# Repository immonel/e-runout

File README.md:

# e-runout

This project is used to measure electrical runout by comparing measurements from touching probe sensors and Eddy current probes simultaneously.

Technologies and frameworks used in the project include Docker, React, Redux, Bootstrap, Node.js, Express, MongoDB and Socket.IO.

### Project structure
[client/](client/)  
Frontend React app code

[documentation/](documentation/)  
Documentation files

[hardware/](hardware/)  
PCB schematics

[mongodb/](mongodb/)  
MongoDB init scripts

[server/](server/)  
Backend Node.js app code

[teensy/](teensy/)  
Teensy microcontroller C++ code

----
## Getting started

### Production

1. Fill out environment variables and rename the .env file:
```sh
$ mv .example.env .env
```

2. Start up the docker-compose stack:
```sh
$ docker-compose up
```

**NOTE:** Please keep in mind that buiding the `erunout` Docker image on Raspberry Pi will take a LONG time (~1h).

The application creates a Wi-Fi access point with environment variables `SSID` and `PASSPHRASE` given in the `.env` file.

IP address for the application is `10.0.10.1` by default and can be accessed after connecting to the WLAN network.

```
TODO: WAN access is currently not working on the wireless access point
```

### Development

1. Rename the .env file:
```sh
$ mv .env.example .env
```

2. Start up the development database:
```sh
$ docker-compose -f docker-compose.dev.yml up
```

3. Start up the development backend server (in the `server` folder):
```sh
server $ npm install
server $ npm run dev
```

4. Start up the development frontend server (in `client` folder):
```sh
client $ npm install
client $ npm start
```

5. Navigate to the development app at `localhost:3001`. The backend server is accessible from `localhost:3000` and the database admin interface from `localhost:8081`.

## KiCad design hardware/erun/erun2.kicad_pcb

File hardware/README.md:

# PCB schematics

This folder contains the KiCad (6.0) schematics for the project. The most recent schematics are named `erun2`. The project file is `erun2.kicad_pro` which is the easiest way to open all the schematics. The wiring diagram is in `erun2.kicad_sch` and PCB in `erun2.kicad_pcb`.

### Data sheets of components used
- [TXB0108PWR](https://www.ti.com/lit/ds/symlink/txb0108.pdf) Voltage level translator (5V->3.3V)
- [MC3486N](https://www.ti.com/lit/ds/symlink/mc3486.pdf) Differential line receiver
- [MCP3301](https://ww1.microchip.com/downloads/aemDocuments/documents/APID/ProductDocuments/DataSheets/21700E.pdf) 13-bit analog-to-digital converter
- [TPS79147DVBT](https://www.ti.com/lit/ds/symlink/tps79147-ep.pdf) Low-dropout regulator (WARNING: These break really easily due to ESD, be careful with these)

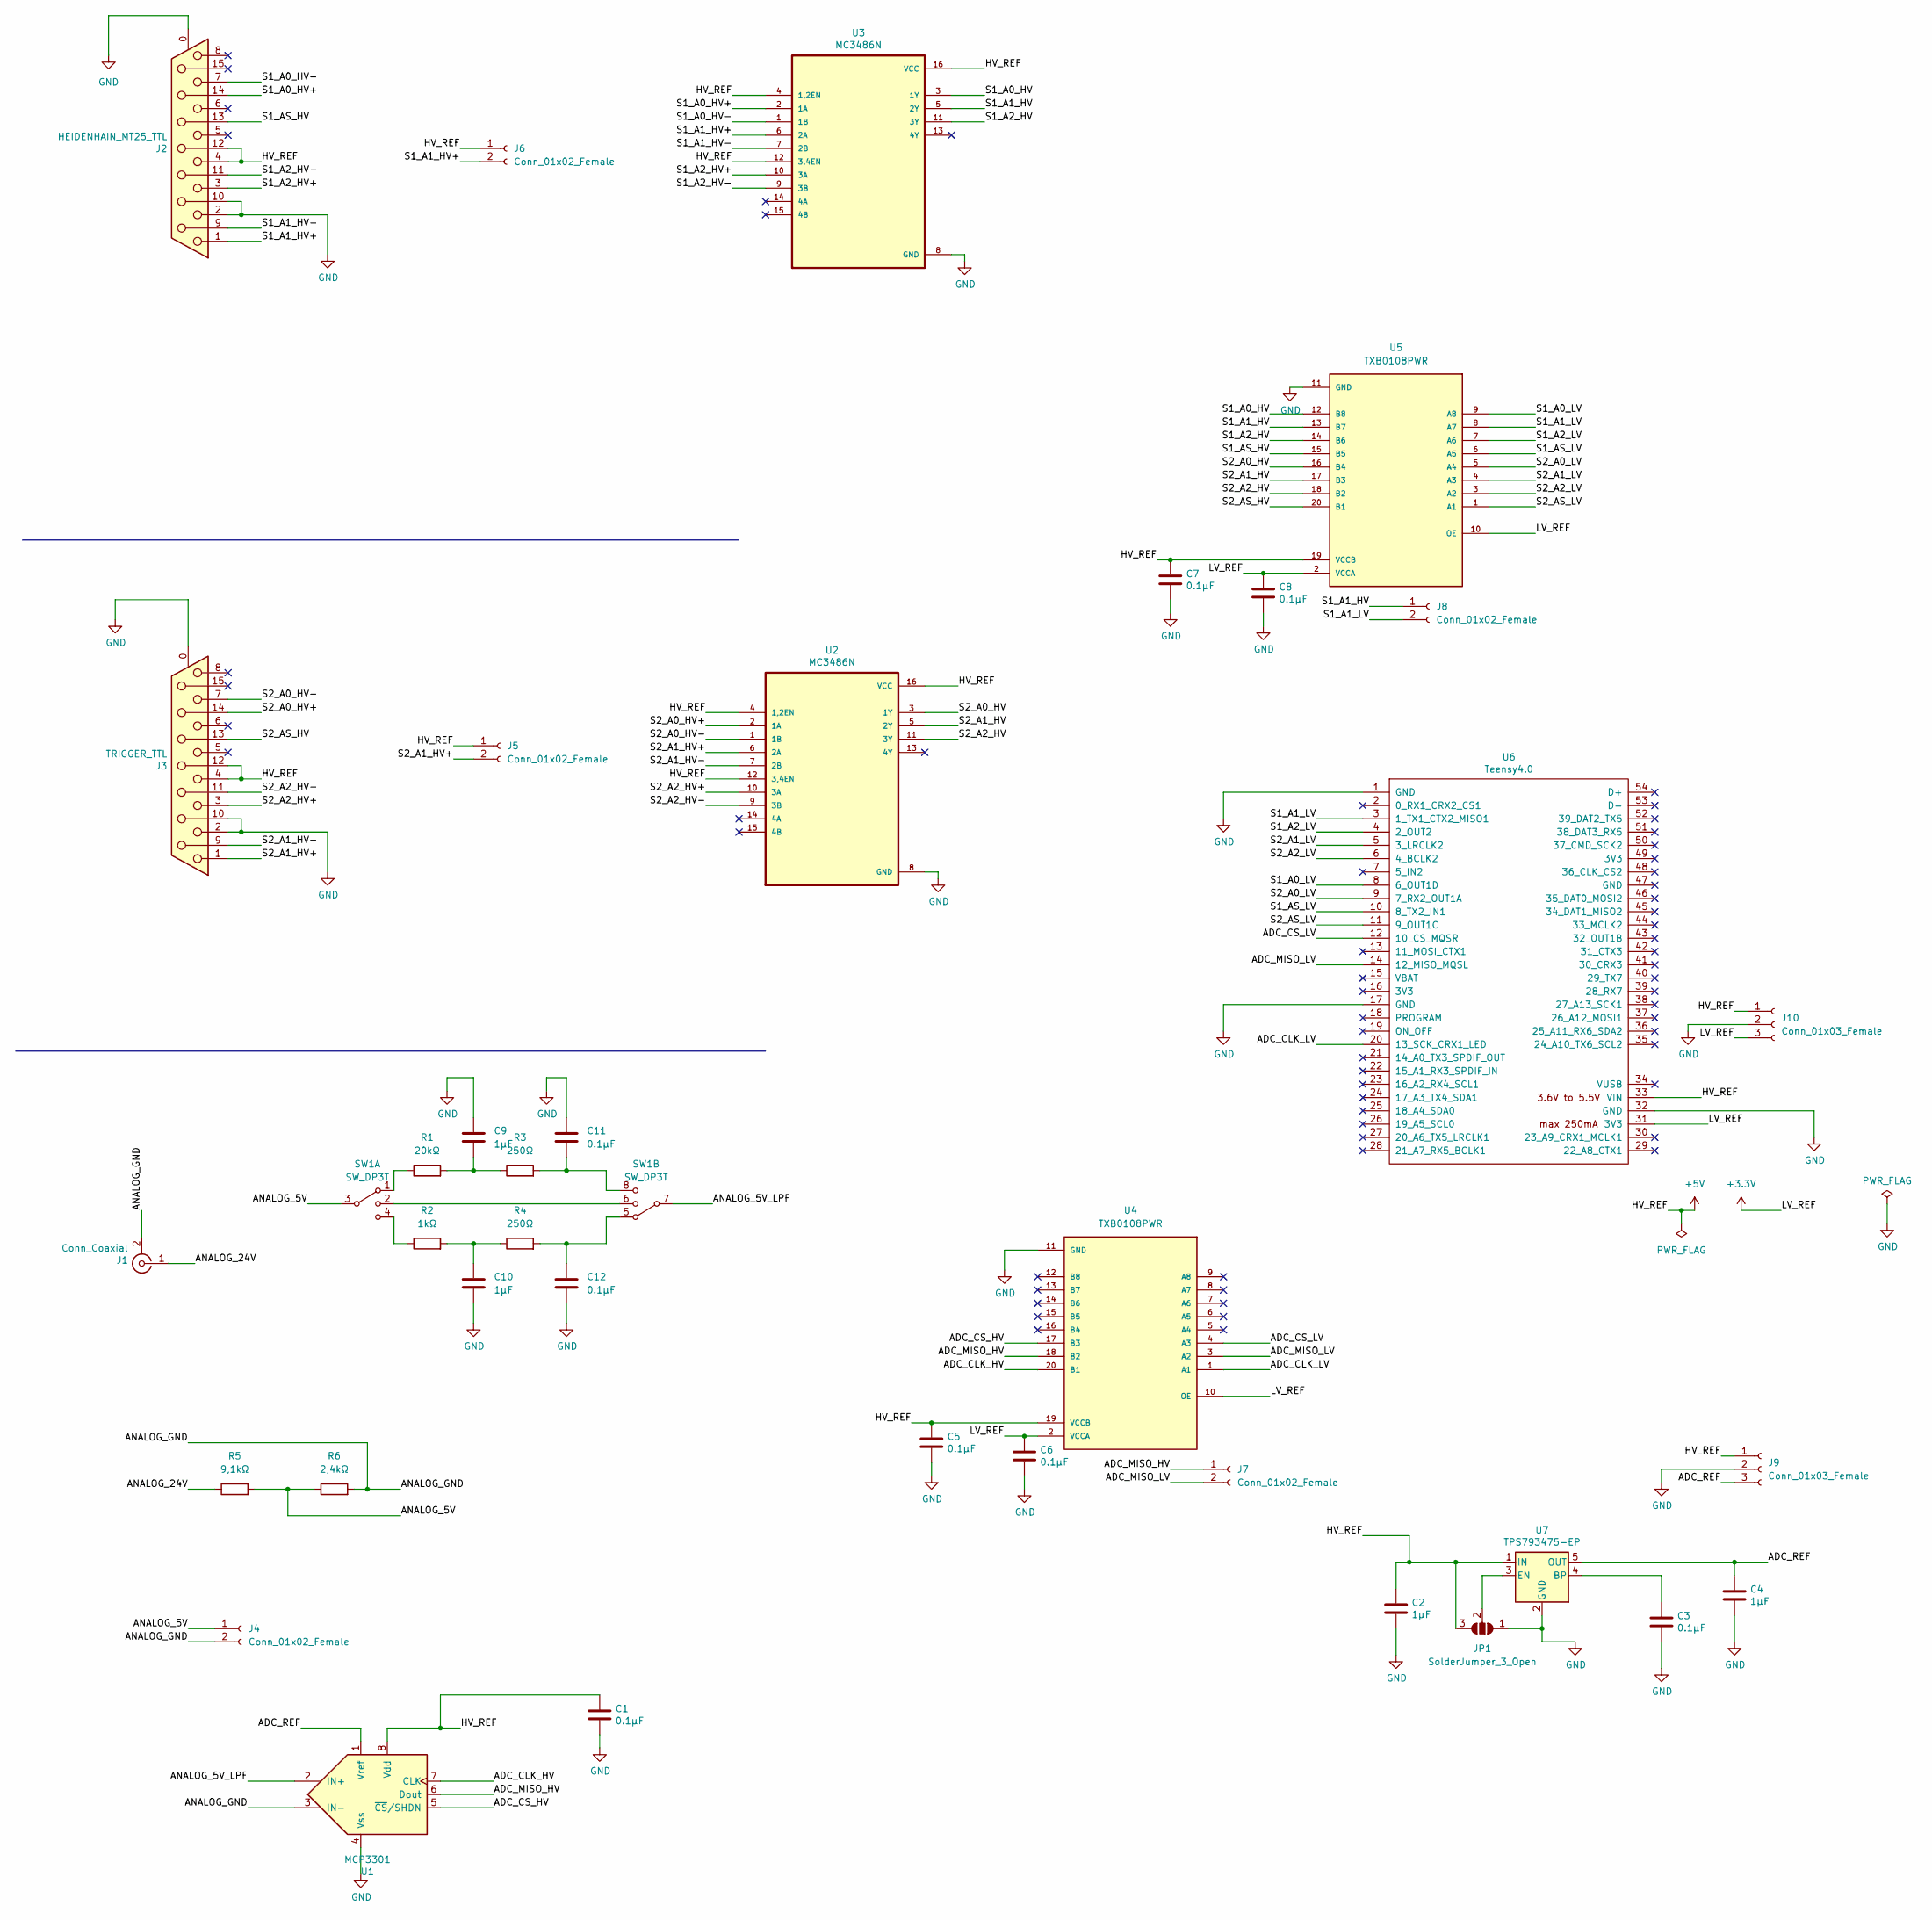
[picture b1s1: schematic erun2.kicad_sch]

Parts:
C1, C3, C5, C6, C7, C8, C11, C12: 0.1μF; C_0603_1608Metric
C2, C4, C9, C10: 1μF; C_0603_1608Metric
J1: Conn_Coaxial; SMA_Amphenol_132134-16_Vertical
J2: HEIDENHAIN_MT25_TTL; DSUB-15_Female_Horizontal_P2.77x2.84mm_EdgePinOffset7.70mm_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
J3: TRIGGER_TTL; DSUB-15_Female_Horizontal_P2.77x2.84mm_EdgePinOffset7.70mm_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
J4, J5, J6, J7, J8: Conn_01x02_Female; PinHeader_1x02_P2.54mm_Vertical
J9, J10: Conn_01x03_Female; PinHeader_1x03_P2.54mm_Vertical
JP1: SolderJumper_3_Open; SolderJumper-3_P1.3mm_Open_Pad1.0x1.5mm_NumberLabels
R1: 20kΩ; R_0603_1608Metric
R2: 1kΩ; R_0603_1608Metric
R3, R4: 250Ω; R_0603_1608Metric
R5: 9,1kΩ; R_0603_1608Metric
R6: 2,4kΩ; R_0603_1608Metric
SW1: SW_DP3T
U1: MCP3301; SOIC-8_3.9x4.9mm_P1.27mm
U2, U3: MC3486N; SOIC-16_4.55x10.3mm_P1.27mm
U4, U5: TXB0108PWR; SOP65P640X120-20N; PARTREV H
U6: Teensy4.0; Teensy40
U7: TPS793475-EP; SOT-23-5

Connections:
+3V3: C6.1, C8.1, J10.3, U4.2 (VCCA), U4.10 (OE), U5.2 (VCCA), U5.10 (OE), U6.31 (3V3)
+5V: C1.1, C2.1, C5.1, C7.1, J2.4, J2.12, J3.4, J3.12, J5.1, J6.1, J9.1, J10.1, JP1.3 (B), U1.8 (Vdd), U2.4 (1,2EN), U2.12 (3,4EN), U2.16 (VCC), U3.4 (1,2EN), U3.12 (3,4EN), U3.16 (VCC), U4.19 (VCCB), U5.19 (VCCB), U6.33 (VIN), U7.1 (IN)
/ADC_CLK_HV: U1.7 (CLK), U4.20 (B1)
/ADC_CLK_LV: U4.1 (A1), U6.20 (13_SCK_CRX1_LED)
/ADC_CS_HV: U1.5 (~CS/SHDN), U4.17 (B3)
/ADC_CS_LV: U4.4 (A3), U6.12 (10_CS_MQSR)
/ADC_MISO_HV: J7.1, U1.6 (Dout), U4.18 (B2)
/ADC_MISO_LV: J7.2, U4.3 (A2), U6.14 (12_MISO_MQSL)
/ADC_REF: C4.1, J9.3, U1.1 (Vref), U7.5 (OUT)
/ANALOG_5V: J4.1, R5.2, R6.1, SW1.3
/ANALOG_5V_LPF: SW1.7, U1.2 (IN+)
/ANALOG_24V: J1.1 (In), R5.1
/ANALOG_GND: J1.2 (Ext), J4.2, R6.2, U1.3 (IN-)
/S1_A0_HV: U3.3 (1Y), U5.12 (B8)
/S1_A0_HV+: J2.14, U3.2 (1A)
/S1_A0_HV-: J2.7, U3.1 (1B)
/S1_A0_LV: U5.9 (A8), U6.8 (6_OUT1D)
/S1_A1_HV: J8.1, U3.5 (2Y), U5.13 (B7)
/S1_A1_HV+: J2.1, J6.2, U3.6 (2A)
/S1_A1_HV-: J2.9, U3.7 (2B)
/S1_A1_LV: J8.2, U5.8 (A7), U6.3 (1_TX1_CTX2_MISO1)
/S1_A2_HV: U3.11 (3Y), U5.14 (B6)
/S1_A2_HV+: J2.3, U3.10 (3A)
/S1_A2_HV-: J2.11 (P111), U3.9 (3B)
/S1_A2_LV: U5.7 (A6), U6.4 (2_OUT2)
/S1_AS_HV: J2.13, U5.15 (B5)
/S1_AS_LV: U5.6 (A5), U6.10 (8_TX2_IN1)
/S2_A0_HV: U2.3 (1Y), U5.16 (B4)
/S2_A0_HV+: J3.14, U2.2 (1A)
/S2_A0_HV-: J3.7, U2.1 (1B)
/S2_A0_LV: U5.5 (A4), U6.9 (7_RX2_OUT1A)
/S2_A1_HV: U2.5 (2Y), U5.17 (B3)
/S2_A1_HV+: J3.1, J5.2, U2.6 (2A)
/S2_A1_HV-: J3.9, U2.7 (2B)
/S2_A1_LV: U5.4 (A3), U6.5 (3_LRCLK2)
/S2_A2_HV: U2.11 (3Y), U5.18 (B2)
/S2_A2_HV+: J3.3, U2.10 (3A)
/S2_A2_HV-: J3.11 (P111), U2.9 (3B)
/S2_A2_LV: U5.3 (A2), U6.6 (4_BCLK2)
/S2_AS_HV: J3.13, U5.20 (B1)
/S2_AS_LV: U5.1 (A1), U6.11 (9_OUT1C)
GND: C1.2, C2.2, C3.2, C4.2, C5.2, C6.2, C7.2, C8.2, C9.1, C10.2, C11.1, C12.2, J2.0 (PAD), J2.2, J2.10, J3.0 (PAD), J3.2, J3.10, J9.2, J10.2, JP1.1 (A), U1.4 (Vss), U2.8 (GND), U3.8 (GND), U4.11 (GND), U5.11 (GND), U6.1 (GND), U6.17 (GND), U6.32 (GND), U7.2 (GND)
unnamed: C3.1, U7.4 (BP)
unnamed: C9.2, R1.2, R3.1
unnamed: C10.1, R2.2, R4.1
unnamed: C11.2, R3.2, SW1.8
unnamed: C12.1, R4.2, SW1.5
unnamed: JP1.2 (C), U7.3 (EN)
unnamed: R1.1, SW1.1
unnamed: R2.1, SW1.4
unnamed: SW1.2, SW1.6

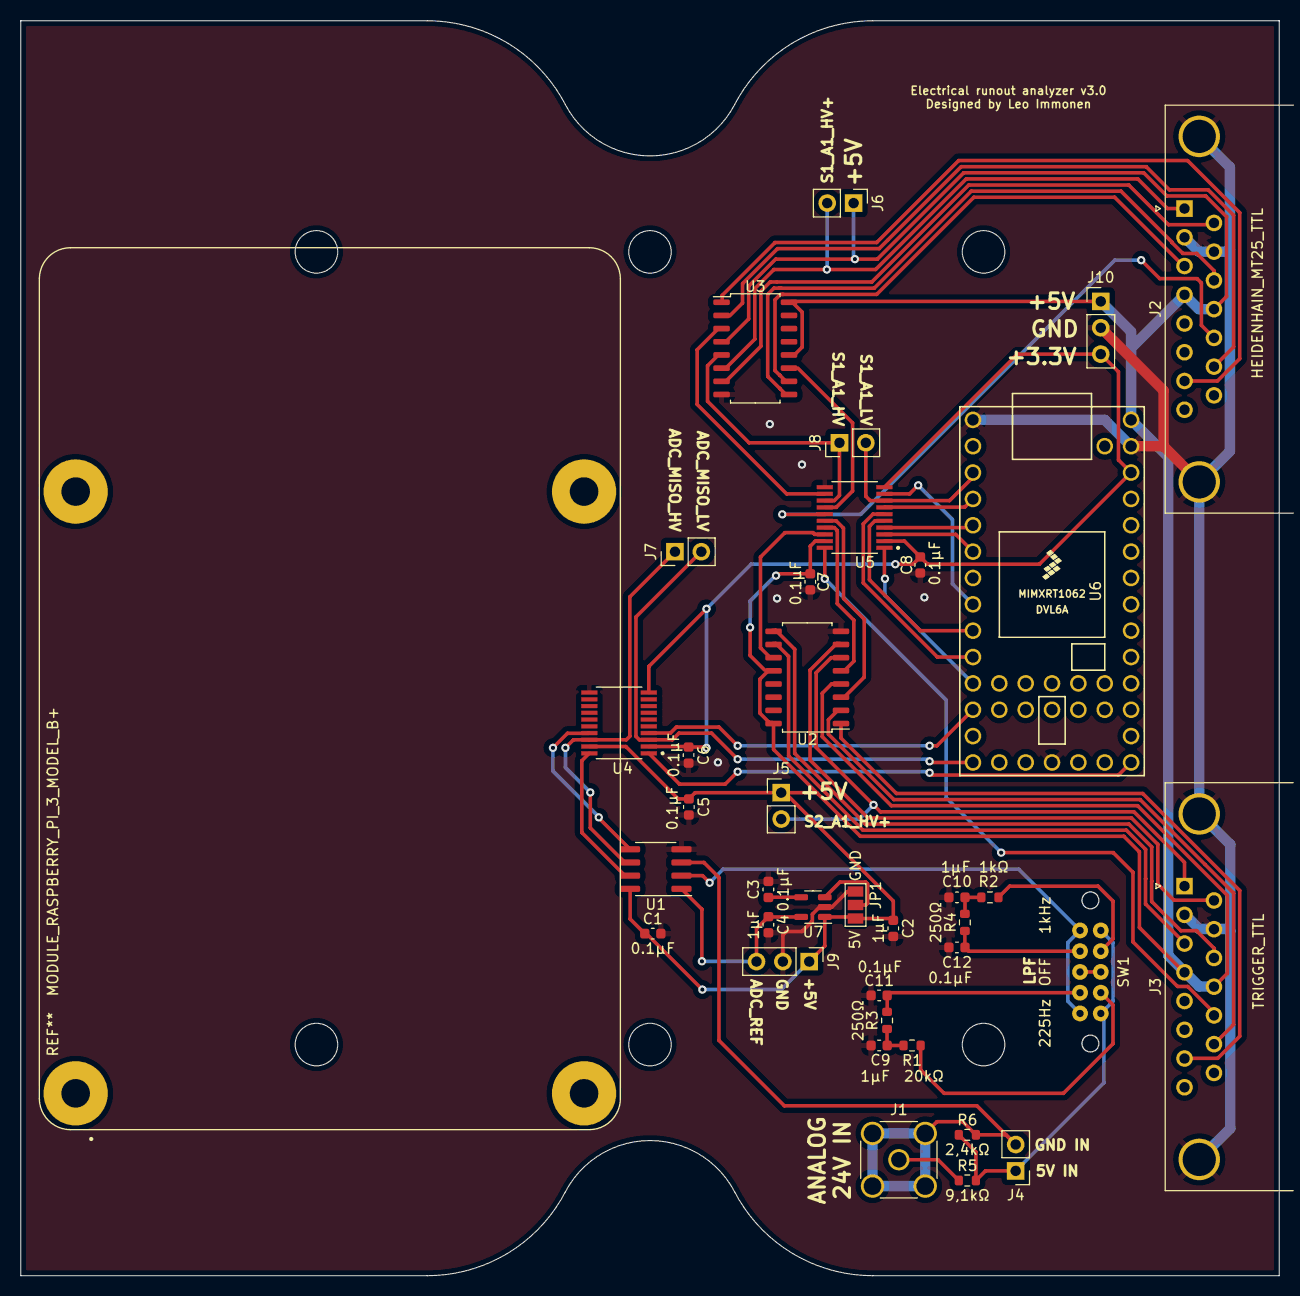
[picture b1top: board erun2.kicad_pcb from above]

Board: 2 copper layers, 121.2 x 120.8 mm, 37 parts (0 on the bottom side), 51 nets.

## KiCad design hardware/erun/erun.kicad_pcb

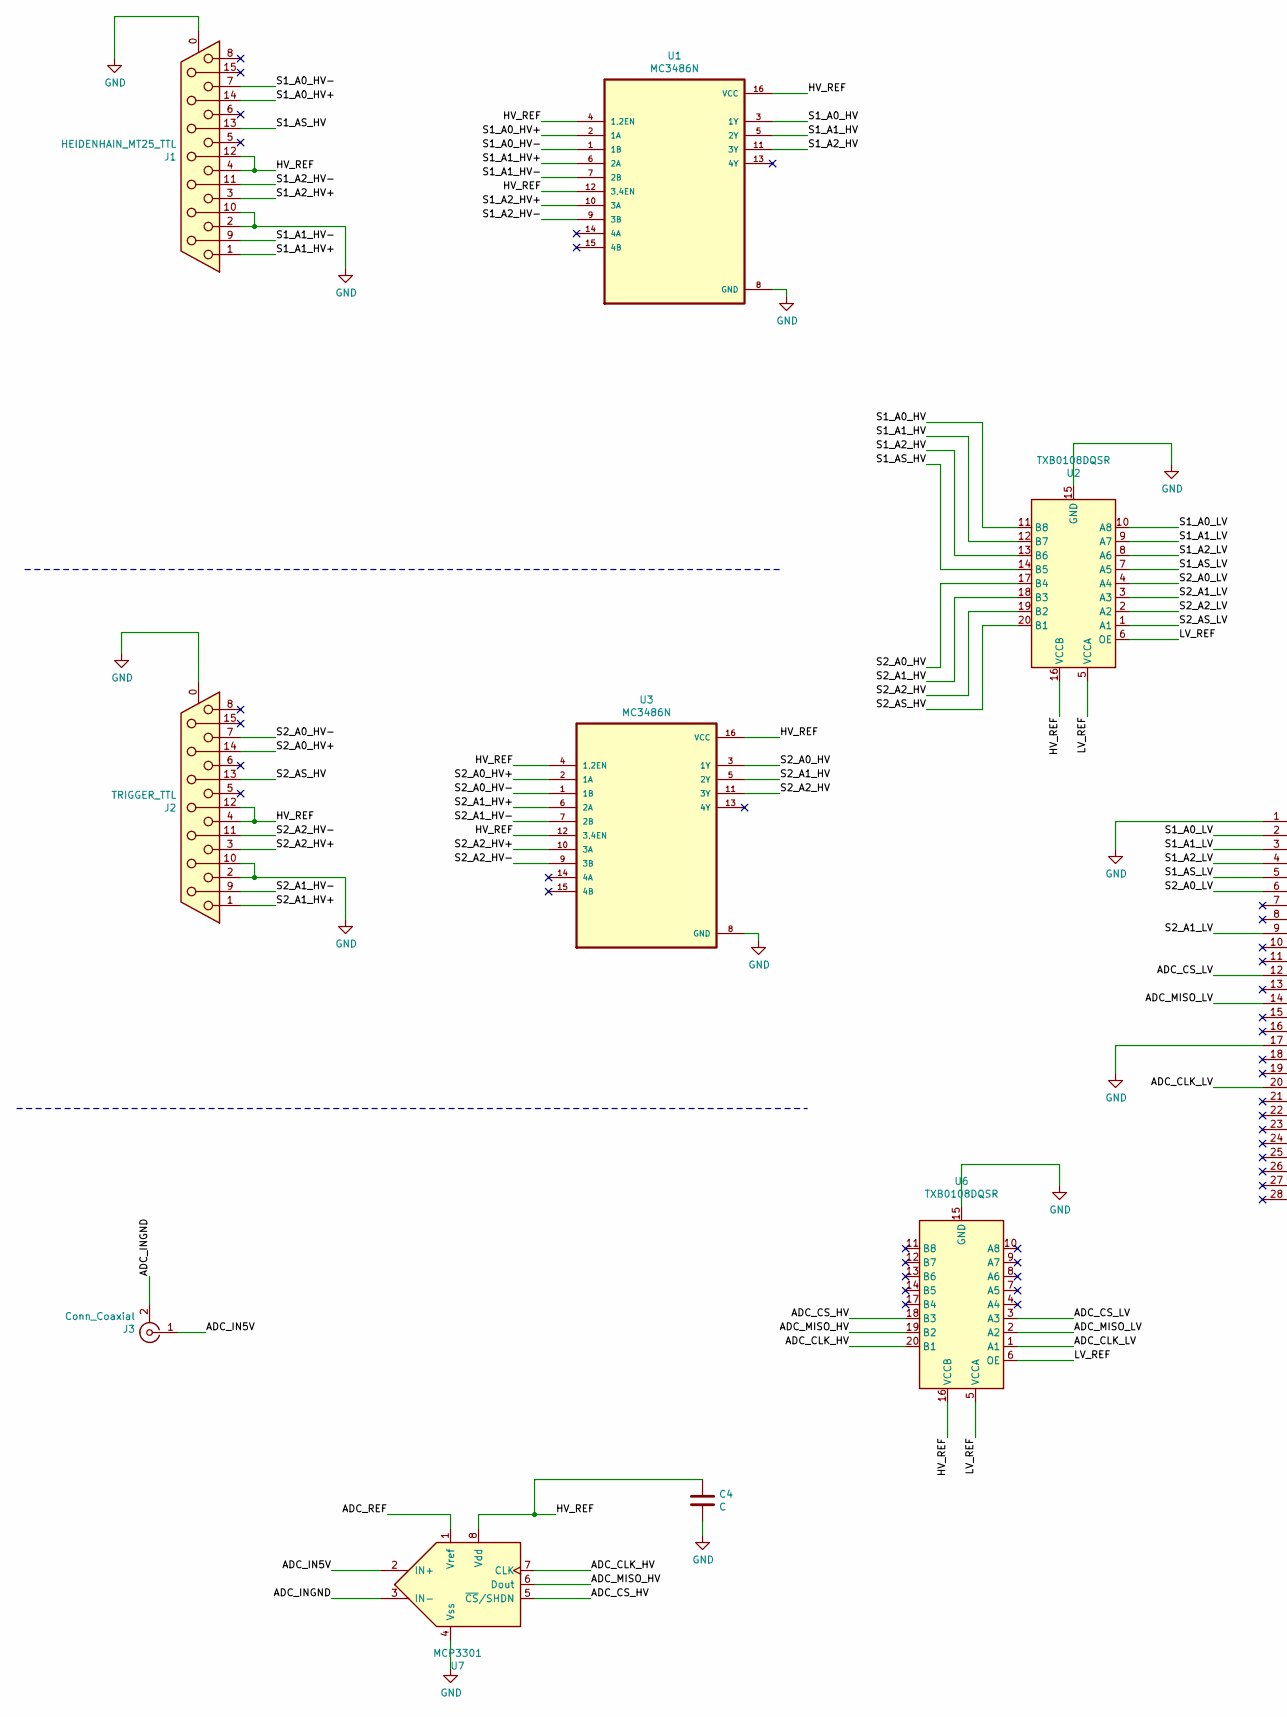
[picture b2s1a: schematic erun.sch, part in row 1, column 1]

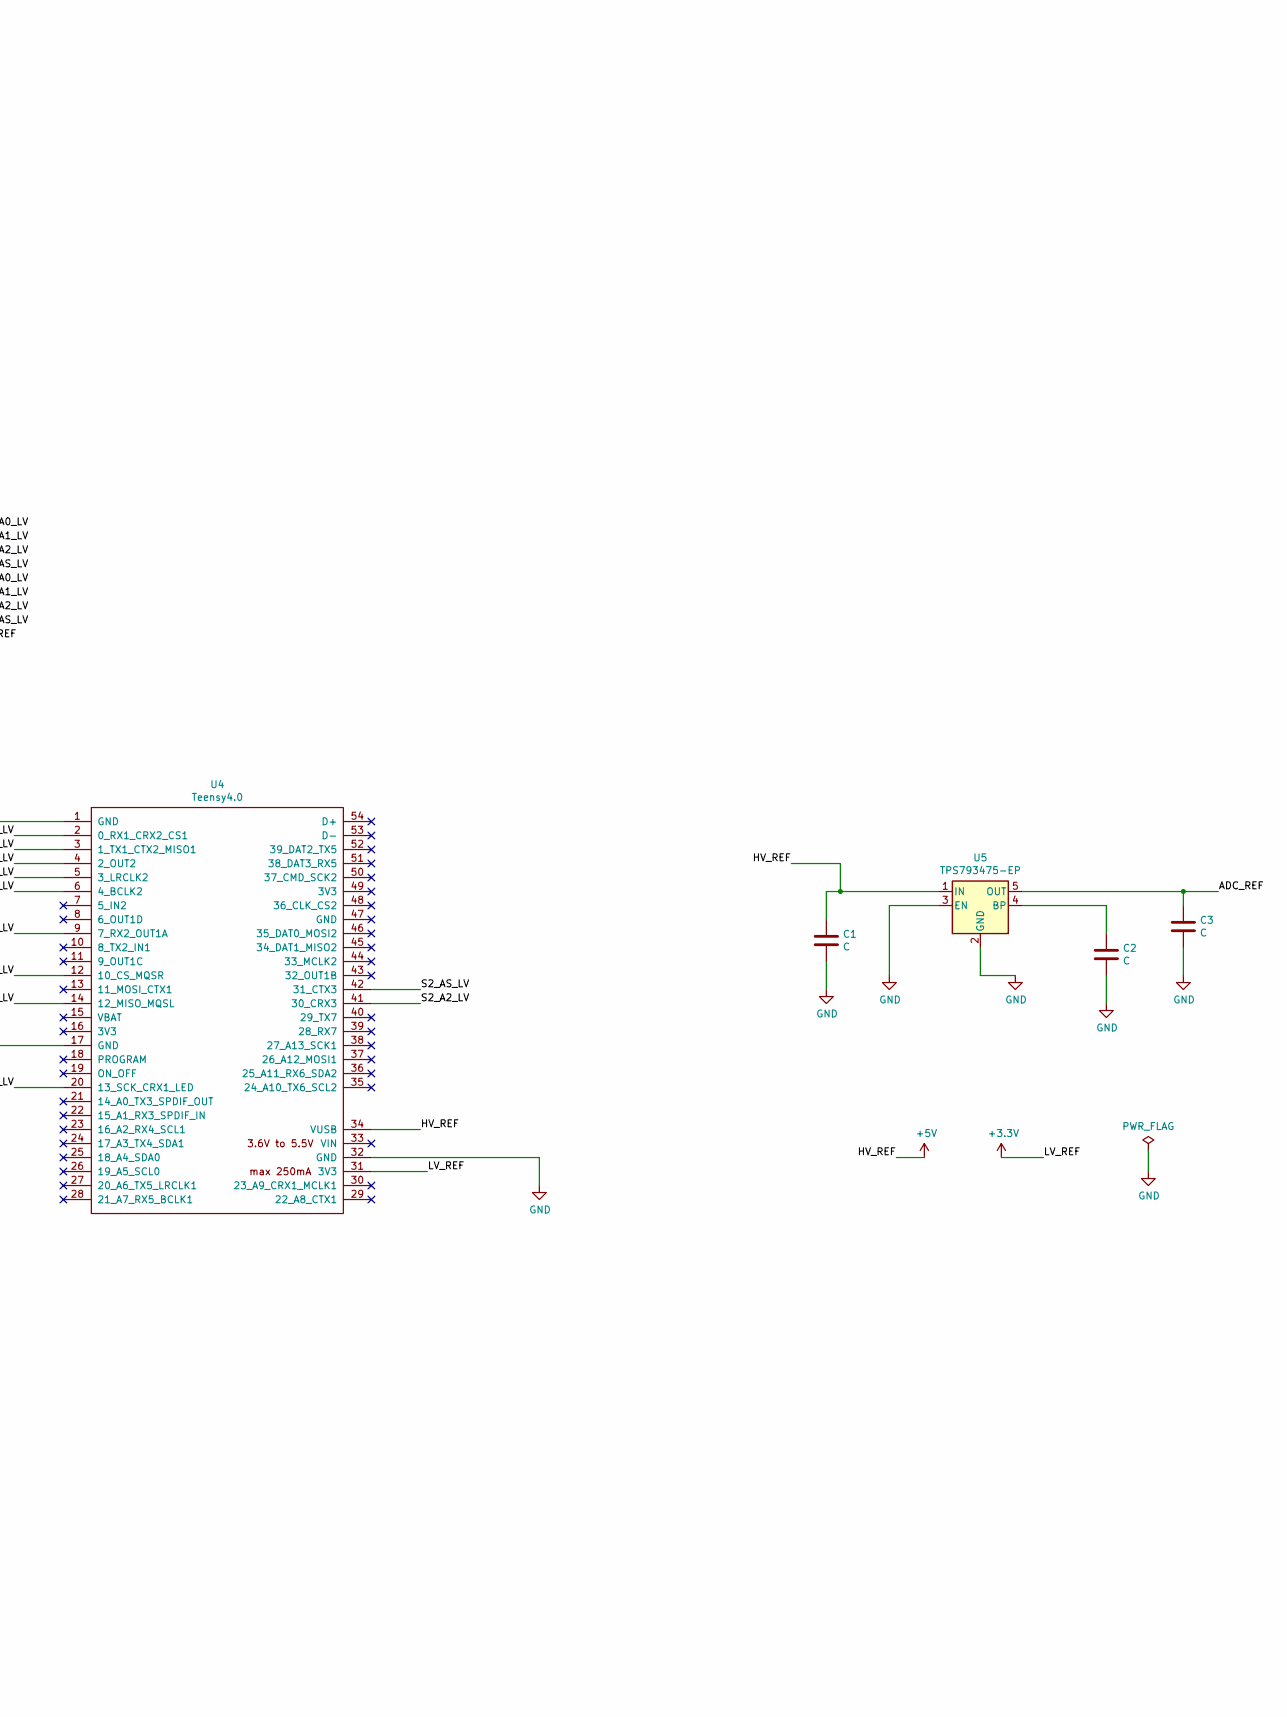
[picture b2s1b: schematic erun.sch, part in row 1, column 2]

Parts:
C1, C2, C3, C4: C; C_0603_1608Metric
J1: HEIDENHAIN_MT25_TTL; DSUB-15_Female_Horizontal_P2.77x2.84mm_EdgePinOffset7.70mm_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
J2: TRIGGER_TTL; DSUB-15_Female_Horizontal_P2.77x2.84mm_EdgePinOffset7.70mm_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
J3: Conn_Coaxial; SMA_Amphenol_132134-14_Vertical
U1, U3: MC3486N; SOIC-16_4.55x10.3mm_P1.27mm
U2, U6: TXB0108DQSR; TSSOP-20_4.4x6.5mm_P0.65mm
U4: Teensy4.0; Teensy40
U5: TPS793475-EP; SOT-23-5
U7: MCP3301; MSOP-8_3x3mm_P0.65mm

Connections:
+3V3: U2.5 (VCCA), U2.6 (OE), U4.31 (3V3), U6.5 (VCCA), U6.6 (OE)
+5V: C1.1, C4.1, J1.4, J1.12, J2.4, J2.12, U1.4 (1,2EN), U1.12 (3,4EN), U1.16 (VCC), U2.16 (VCCB), U3.4 (1,2EN), U3.12 (3,4EN), U3.16 (VCC), U4.34 (VUSB), U5.1 (IN), U6.16 (VCCB), U7.8 (Vdd)
/ADC_CLK_HV: U6.20 (B1), U7.7 (CLK)
/ADC_CLK_LV: U4.20 (13_SCK_CRX1_LED), U6.1 (A1)
/ADC_CS_HV: U6.18 (B3), U7.5 (~CS~/SHDN)
/ADC_CS_LV: U4.12 (10_CS_MQSR), U6.3 (A3)
/ADC_IN5V: J3.1 (In), U7.2 (IN+)
/ADC_INGND: J3.2 (Ext), U7.3 (IN-)
/ADC_MISO_HV: U6.19 (B2), U7.6 (Dout)
/ADC_MISO_LV: U4.14 (12_MISO_MQSL), U6.2 (A2)
/ADC_REF: C3.1, U5.5 (OUT), U7.1 (Vref)
/S1_A0_HV: U1.3 (1Y), U2.11 (B8)
/S1_A0_HV+: J1.14, U1.2 (1A)
/S1_A0_HV-: J1.7, U1.1 (1B)
/S1_A0_LV: U2.10 (A8), U4.2 (0_RX1_CRX2_CS1)
/S1_A1_HV: U1.5 (2Y), U2.12 (B7)
/S1_A1_HV+: J1.1, U1.6 (2A)
/S1_A1_HV-: J1.9, U1.7 (2B)
/S1_A1_LV: U2.9 (A7), U4.3 (1_TX1_CTX2_MISO1)
/S1_A2_HV: U1.11 (3Y), U2.13 (B6)
/S1_A2_HV+: J1.3, U1.10 (3A)
/S1_A2_HV-: J1.11 (P111), U1.9 (3B)
/S1_A2_LV: U2.8 (A6), U4.4 (2_OUT2)
/S1_AS_HV: J1.13, U2.14 (B5)
/S1_AS_LV: U2.7 (A5), U4.5 (3_LRCLK2)
/S2_A0_HV: U2.17 (B4), U3.3 (1Y)
/S2_A0_HV+: J2.14, U3.2 (1A)
/S2_A0_HV-: J2.7, U3.1 (1B)
/S2_A0_LV: U2.4 (A4), U4.6 (4_BCLK2)
/S2_A1_HV: U2.18 (B3), U3.5 (2Y)
/S2_A1_HV+: J2.1, U3.6 (2A)
/S2_A1_HV-: J2.9, U3.7 (2B)
/S2_A1_LV: U2.3 (A3), U4.9 (7_RX2_OUT1A)
/S2_A2_HV: U2.19 (B2), U3.11 (3Y)
/S2_A2_HV+: J2.3, U3.10 (3A)
/S2_A2_HV-: J2.11 (P111), U3.9 (3B)
/S2_A2_LV: U2.2 (A2), U4.41 (30_CRX3)
/S2_AS_HV: J2.13, U2.20 (B1)
/S2_AS_LV: U2.1 (A1), U4.42 (31_CTX3)
GND: C1.2, C2.2, C3.2, C4.2, J1.0 (PAD), J1.2, J1.10, J2.0 (PAD), J2.2, J2.10, U1.8 (GND), U2.15 (GND), U3.8 (GND), U4.1 (GND), U4.17 (GND), U4.32 (GND), U5.2 (GND), U5.3 (EN), U6.15 (GND), U7.4 (Vss)
unnamed: C2.1, U5.4 (BP)

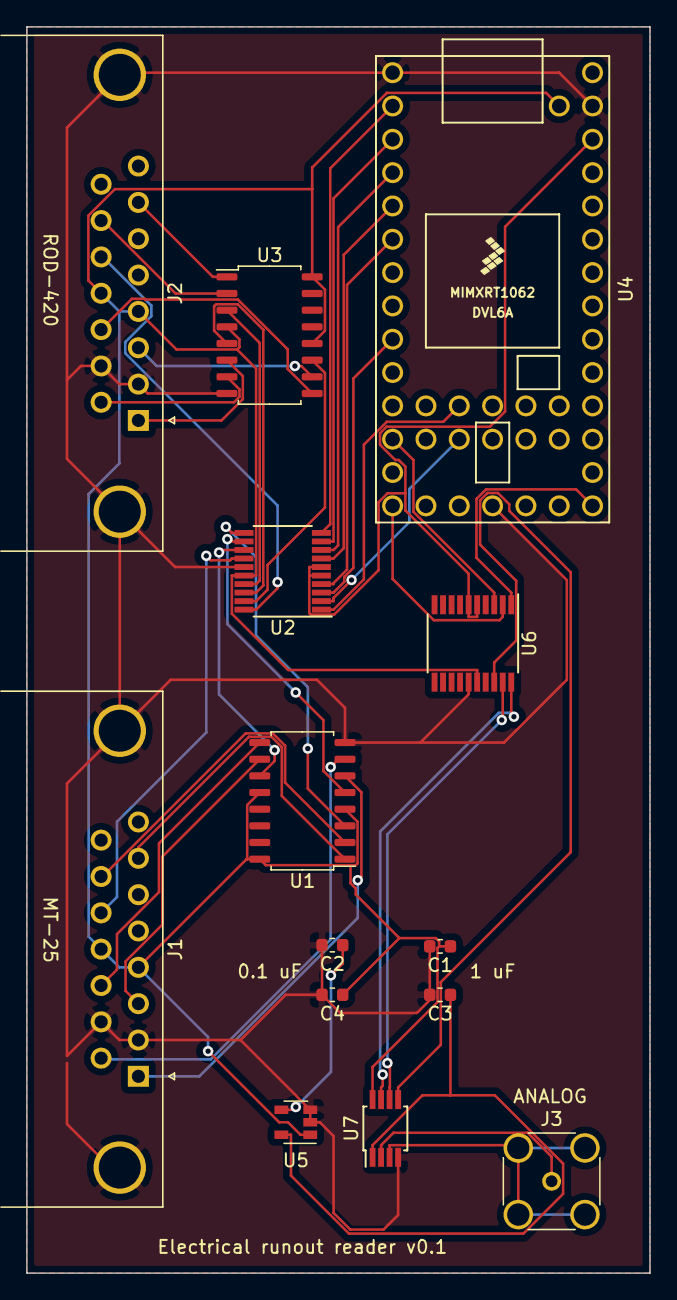
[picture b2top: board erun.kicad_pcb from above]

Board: 2 copper layers, 47.5 x 95.0 mm, 14 parts (0 on the bottom side), 41 nets.

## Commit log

2021-11-10 start work on schematic
2021-11-18 hardware
2021-11-18 Added teensy code
2021-11-18 Updated schematic
2021-11-26 Updated schematics
2021-11-27 Updated schematics and PCB design
2021-12-01 Updated schema
2021-12-01 erun updates
2021-12-01 E-runout HW v0.1
2021-12-15 Added first version of webapp
2022-02-06 Added support for serial port data input
2022-02-11 Minor changes
2022-03-17 Board version 2.0
2022-03-23 Fixed clearance issues
2022-03-23 Fixed some more clearance issues
2022-03-24 Added capacitors to the board
2022-03-24 Added filled zones
2022-03-24 Added vias to filled zones
2022-03-24 Fixed a label
2022-04-13 Added low pass filter and minor refinements
2022-04-14 Updated some labels
2022-04-14 Very minor fixes
2022-04-19 Disabled automatic reconnecting
2022-05-04 Added page for calibration
2022-05-19 Added backend support for zeroing the encoder
2022-05-19 Average is now substracted from plotted measurement data
2022-05-25 PCB 2.1, fixed ADC and moved analog input
2022-05-31 Added reading from actual sensors
2022-06-02 Added docker-compose
2022-06-07 Added webapp support for real sensor values and coefficients
2022-06-08 Added chart optimizations
2022-06-08 Overhauled backend code structure
2022-06-08 Fixed bug where the stop command did not work
2022-06-13 Added support for different sampling modes
2022-06-13 Fixed serial connection status
2022-06-13 Added calibration plotting and regression
2022-06-13 Refactored app to use redux
2022-06-13 Improved chart performance
2022-06-13 Fixed config modifying
2022-06-13 Calibrations can now be selected
2022-06-13 Added sensor name inputs
2022-06-20 Disabled button for invalid calibrations
2022-06-20 Added frontend support for creating empty calibrations
2022-06-20 Refactored backend to support creating empty measurements and appending measurements
2022-06-20 Starting measurement on calibration tab now appends to an existing calibration
2022-06-20 Changed card title
2022-06-20 Moved files to another folder
2022-06-20 Removed sample speed
2022-06-20 Moved storing start time to backend
2022-06-20 Combined duplicate code
2022-06-21 Cleaned up frontend code
2022-06-23 Added id and additional properties for a measurement
    Squash: Added id and flexible fields to measurements
2022-06-23 Measurements and calibrations are now split in frotend
    Squash: Measurements and calibrations are now stored in one place
2022-06-23 Added support for deleting all calibrations
2022-06-23 Measurements are now handled by their ID
2022-06-23 JSON files are now accessible through blobs
2022-06-23 Removed HTTP api
2022-06-23 Added reconnection interval for serial port
2022-06-27 Improved teensy responsiveness by decreasing serial timeout
2022-06-27 Reduced unnecessary rerenders during measurement
2022-06-27 Revamped measurement data structure and calibration
2022-06-28 Added control buttons for MCU connection
2022-06-28 Added ability to fetch raw measurement data from server
2022-06-28 Added support for optional configuration values
2022-06-28 Added support for measurement name and component reference
2022-06-28 Improved mobile layout
2022-06-28 Added label to measurement chart
2022-06-28 Measurement updates are now broadcasted to every client
2022-06-28 Added modal for viewing measurement info
2022-06-28 Changed calibration chart colors
2022-07-04 Added voltage divider
2022-07-05 Hid broken download button
2022-07-05 Fixed text input with whitespace
2022-07-05 Updated package-locks
2022-07-05 Downgraded node version
2022-07-05 Added wifi access point container
2022-07-06 Added bootstrap, removed axios and moved dependencies to devdependencies
2022-07-06 Fixed wifi-ap config
2022-07-06 Changed CSS fetching from CDN to local
2022-07-12 Removed file with mock data
2022-07-21 First version of PCB board v3.0
2022-07-22 Added AsyncAPI documentation of WebSocket API
2022-07-26 Changed SW1 hole shape and added analog text
2022-07-27 Fixed trace overlapping with hole and changed MCP3301 package from MSOP to SOIC
2022-08-15 Cleaned up code
2022-08-15 Added frontend README.md
2022-08-15 Changed frontend dev server port
2022-08-16 Added database containers
2022-08-16 Added development database containers
2022-08-16 Updated mongoose schema
2022-08-16 Added database handlers to backend
2022-08-16 Use MongoDB to store measurements
2022-08-16 Use MongoDB ID instead of creating own
2022-08-16 Added informative text for sample count
2022-08-16 Removed mongo-express from production stack
2022-08-16 Added status indicator for database connection
2022-08-16 Added visual badges for connection status
2022-08-16 Removed 'Reconnect MCU' button
2022-08-16 Added info text for dev environment
2022-08-16 Removed unnecessary config file
2022-08-16 Fixed docker-compose
2022-08-16 Added mongo init script
2022-08-17 Starting and stopping measurement with single button
2022-08-17 Sample mode is now changed from a select dropdown
2022-08-17 Modified connection status info texts
2022-08-17 Moved measurement status info to a new component
2022-08-17 Cleaned up CSS
2022-08-17 Moved Measure and Calibrate pages to components folder
2022-08-17 Changed mongodb tag to lower version for compatibility
2022-08-17 Added 'disabled' prop for StartStopButton
2022-08-17 Added selected calibration info text
2022-08-17 Database connection status is updated on server disconnect
2022-08-17 Merged DELETE_CALIBRATIONS call to DELETE_MEASUREMENTS
2022-08-17 Added confirmation to delete all button
2022-08-17 Changed chart label
2022-08-17 Added print button for measurement modal
2022-08-22 Added usage guide
2022-08-22 Added more documentation
2022-08-22 Added compact property
2022-08-22 Added measurement status info to Calibrate tab
2022-08-22 Updated AsyncAPI documentation
2022-08-22 Added screenshot to README.md
2022-08-23 Add documentation/README.md
2022-08-26 Updated documentation
2022-09-10 Added links
